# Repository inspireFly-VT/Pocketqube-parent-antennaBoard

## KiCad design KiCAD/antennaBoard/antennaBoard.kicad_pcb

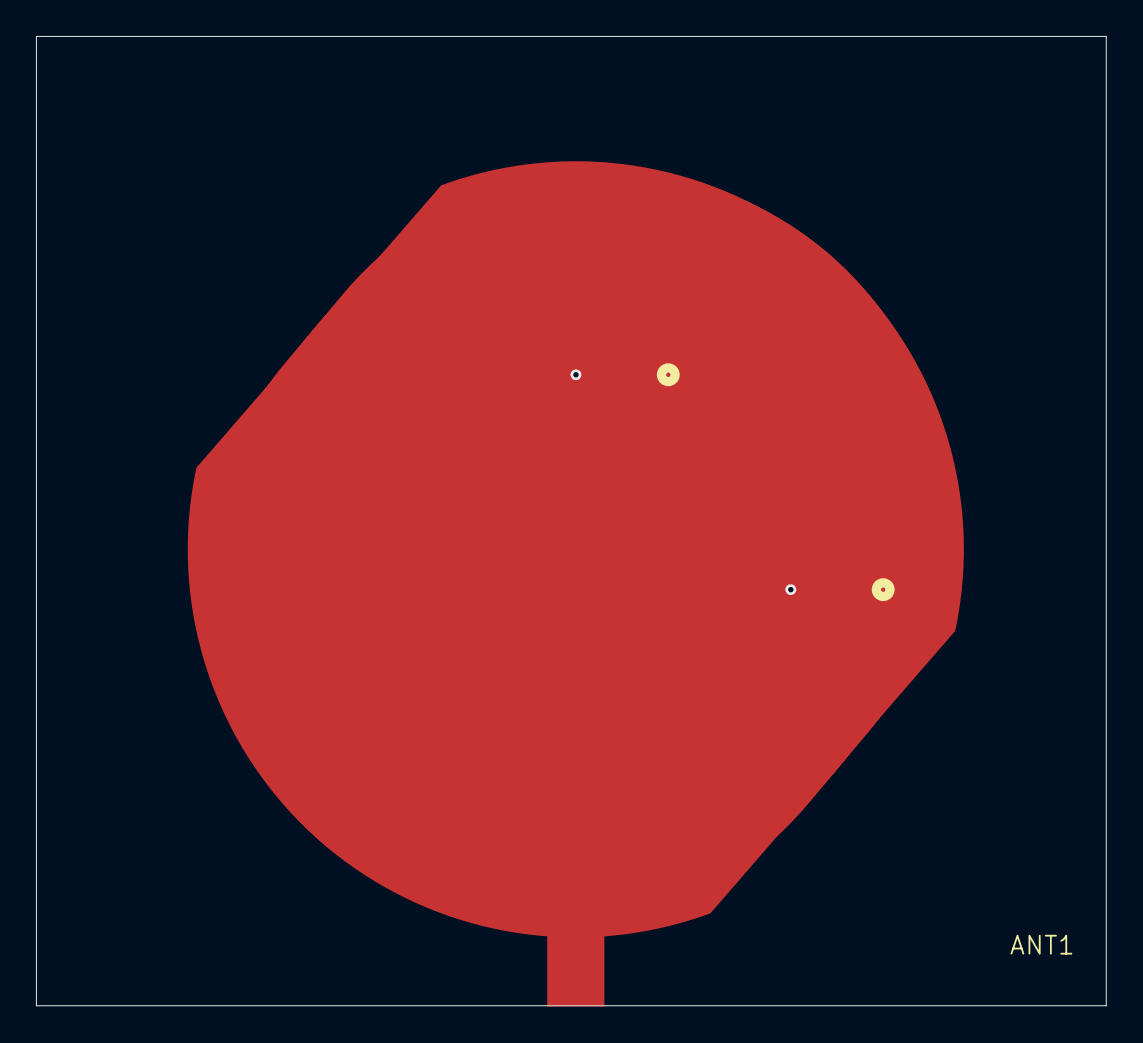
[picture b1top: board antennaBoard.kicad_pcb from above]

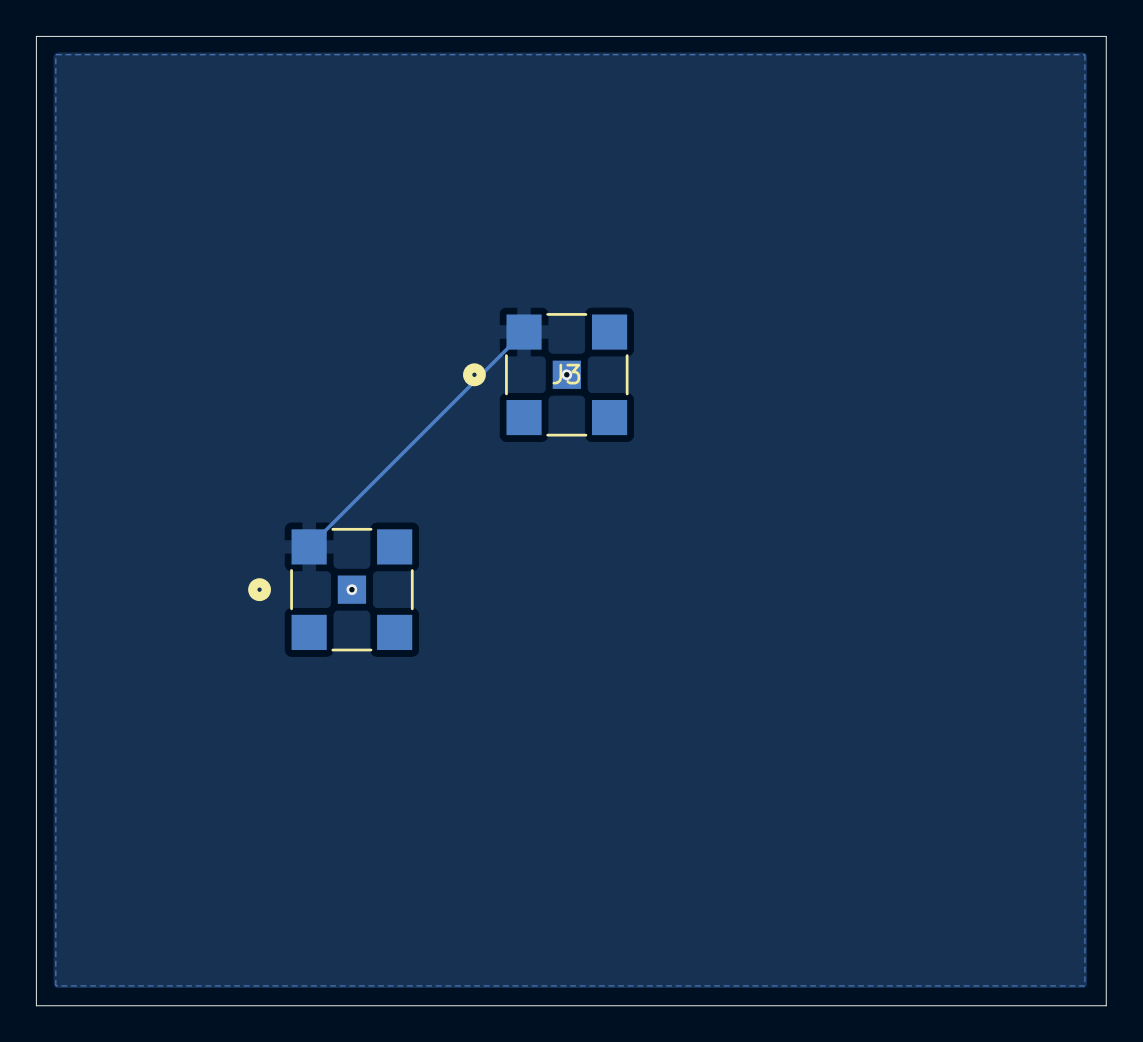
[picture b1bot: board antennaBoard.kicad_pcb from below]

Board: 4 copper layers, 59.4 x 53.8 mm, 3 parts (2 on the bottom side), 2 nets.

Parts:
ANT1: 2.305GHz Patch; CircularPatchAntenna
J1, J3: Conn_Coaxial; CONN_732511350_MOL

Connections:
GND: J1.2 (Ext), J3.2 (Ext)
unnamed: ANT1.1 (A_1), J1.1 (In), J3.1 (In)

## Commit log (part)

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2025-10-21 Move matlab
2025-10-21 Add ansys monopole patch design
    To be circularly polarized. Gain plot is sausage shaped and S-parameter dB drop occurs ~3.42 GHz. Substrate dimensions are 5x5cm and patch dimensions are 39.66 x 30.73 mm. Currently using coax feed, 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
    Next steps would be to adjust the substrate dimensions to fit Pocketqube, and patch so s-parameter dB drops properly around 2.3 GHz mark. Also need to make circularly polarized by cutting the corners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
2025-10-30 Update patch
    Check new dimensions & implementation of microstrip feed.
2025-11-02 Adjust patch material & thickness
    Copper 0.035mm
2025-11-20 Square aperture patch calculations
2025-12-04 Doc Initial commit
    Taken from ttc Inspirefly repo
2025-12-04 Create HexagonalPatch.aedt
    Is CP and has good S11, but gain is questionable and much too big. Size needs to be cut by half
2025-12-04 Create CircularPatch.aedt
    S11 a little off. Gain is acceptable, but on the low side. Size is a bit too big, but can be made to fit, if necessary.
2026-02-19 Create CircularPatchV3.aedt
    Two coax approach for 1U design
2026-03-01 Import patch to KiCAD
2026-04-08 Add coax
2026-04-28 Impl 2 coax feed
    Use external power divider: APS-02-WBM-LP-DF-CC
